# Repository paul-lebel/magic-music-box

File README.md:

# magic-music-box
A small platform for parent-configurable child entertainment and education.

## Features
1. A small box with a simple screen, UI buttons, an audio system, and a lighting system.
2. A software platform that allows parents to create custom quiz questions (eg. "What does 5+5 equal?") or games.
3. A text to speech module reads the input prompts aloud through the audio speaker for children too young to read.
4. A bluetooth module allows for music streaming to the device from a parent's cellphone.
5. Computer control of the lighting system enhances the user experience for the child.
6. Customization of the underlying PCB's silkscreen artwork is displayed through a transparent front panel.

## Requirements
RPi.GPIO, inky, gTTS, circuitpython, adafruit-circuitpython-neopixel, font_fredoka_one

## Installation
This module was developed on Raspberry Pi Zero W V1.1, but should be compatible with all newer RPi models running the latest version of Raspbian OS.
1. Ensure the OS is updated, and also ensure that Python 3 is used by default. Following the instructions here takes care of this as well as circuitpython installation: <br>
https://learn.adafruit.com/circuitpython-on-raspberrypi-linux/installing-circuitpython-on-raspberry-pi
2. Follow these instructions to install inky: <br>
https://learn.pimoroni.com/tutorial/sandyj/getting-started-with-inky-phat
3. Add the following lines to /boot/config.txt: <br>
dtoverlay=audremap, enable_jack=on <br>
dtoverlay=audremap, pins_18_19=on <br>
dtoverlay=spi1-3cs <br>
4. Download / clone this repository
5. Navigate to the base of the repository
6. Install setuptools (__pip install setuptools__)
7. Install module (__pip install .__)

## Updating Module from Repository
1. Pull changes from remote repository
2. Activate virtual environment with previous install
3. Navigate to the module directory
4. Test the module for completeness (__python setup.py test__)
5. Update module (__pip install . --upgrade__)

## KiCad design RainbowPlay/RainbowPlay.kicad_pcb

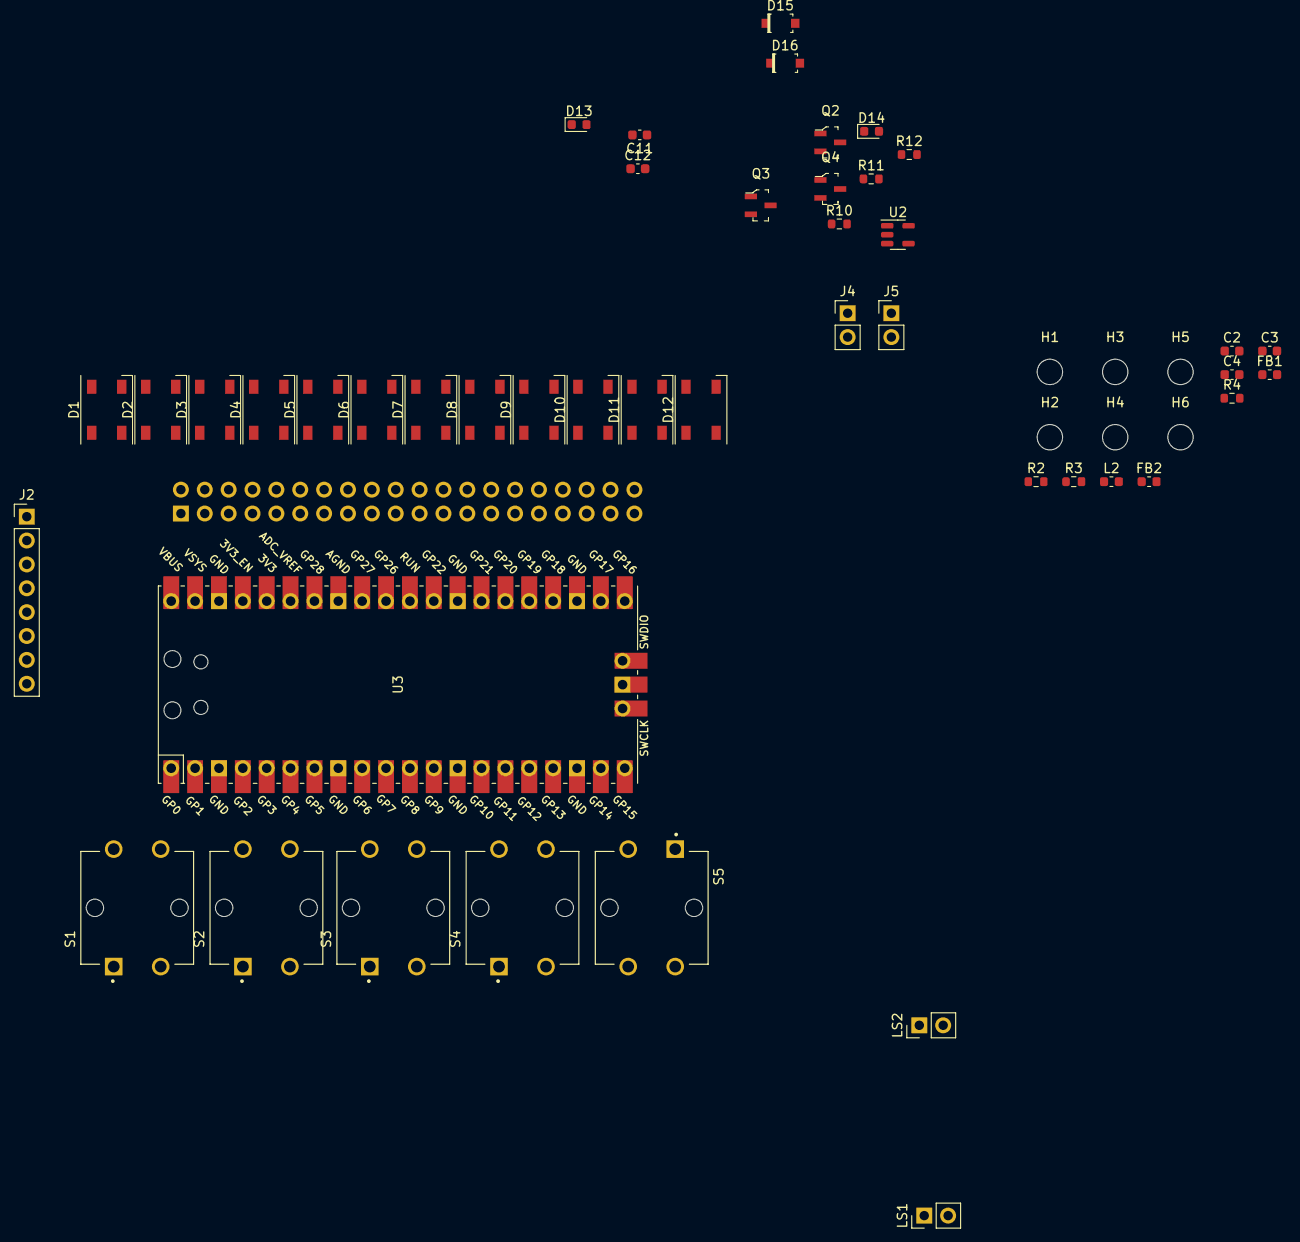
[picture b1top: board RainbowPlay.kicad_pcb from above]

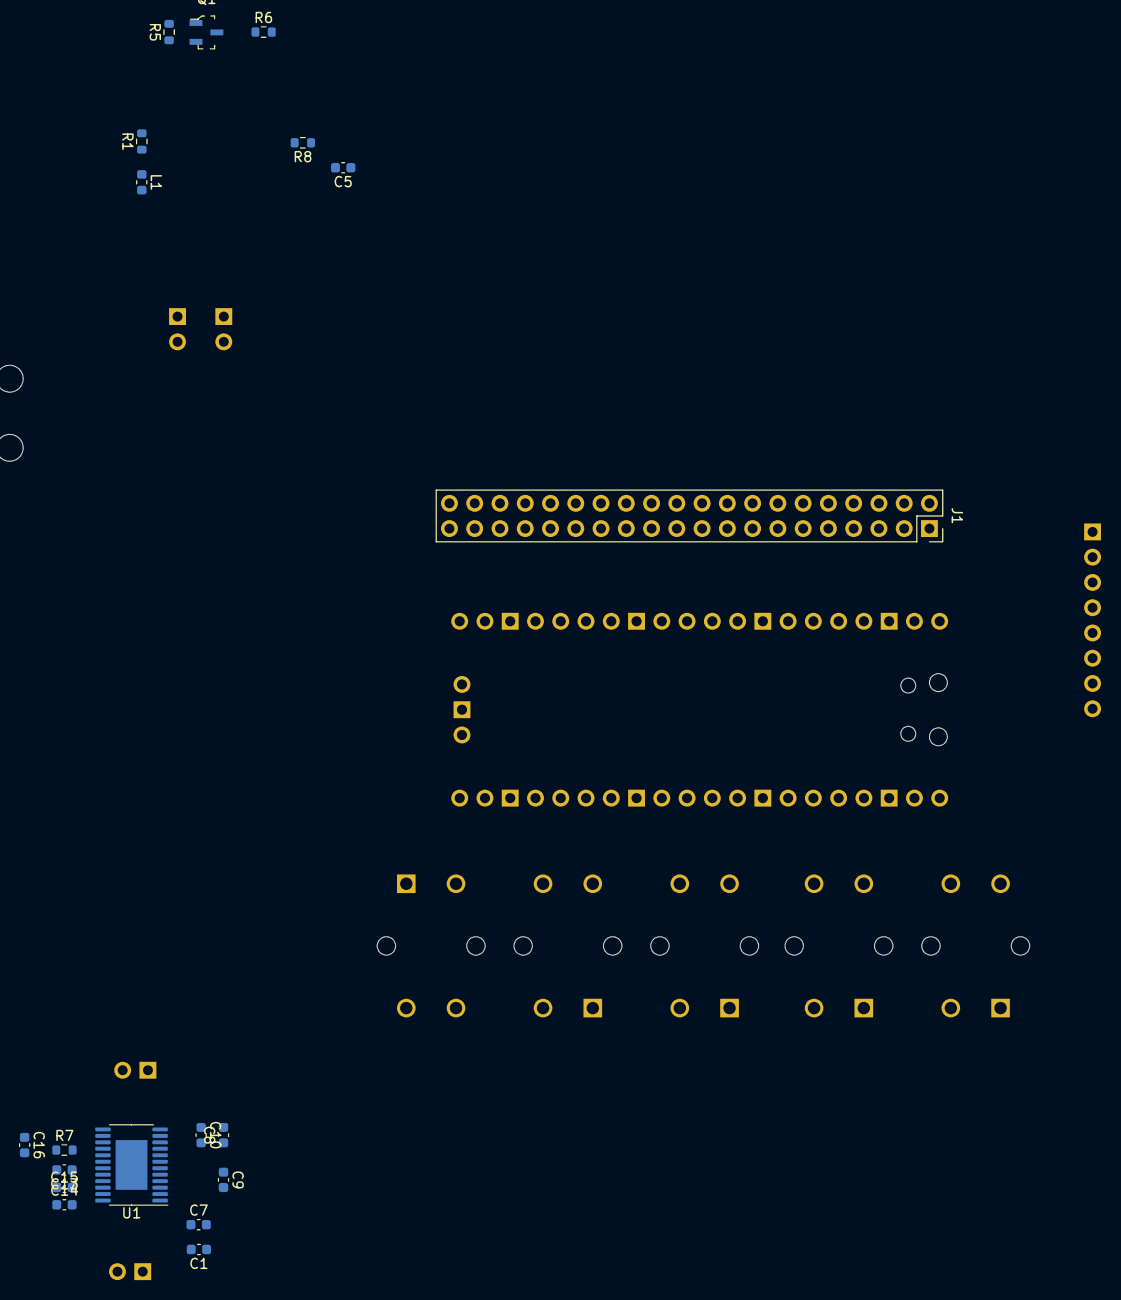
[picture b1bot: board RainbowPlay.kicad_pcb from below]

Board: 4 copper layers, 70 parts (19 on the bottom side), 52 nets, no tracks yet.

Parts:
C1, C2: 1.5uF; C_0603_1608Metric
C3, C4, C5, C7, C15, C16: 10uF; C_0603_1608Metric
C8, C9, C11, C12, C13: 0.1uF; C_0603_1608Metric
C10: 220pF; C_0603_1608Metric
C14: 1uF; C_0603_1608Metric
D1, D2, D3, D4, D5, D6, D7, D8, D9, D10, D11, D12: SK6812; LED_SK6812_PLCC4_5.0x5.0mm_P3.2mm
D13, D14: LED; LED_0603_1608Metric
D15, D16: 1N5819HW-7-F; SOD-123
FB1, FB2: FerriteBead_Small; L_0603_1608Metric
H1, H2, H3, H4, H5, H6: MountingHole; MountingHole_2.7mm
J1: GPIO_CONNECTOR; PinSocket_2x20_P2.54mm_Vertical
J2: Conn_01x08_Male; PinHeader_1x08_P2.54mm_Vertical
J4, J5: Conn_01x02_Male; PinHeader_1x02_P2.54mm_Vertical
L1, L2: 10uH; L_0603_1608Metric
LS1, LS2: Speaker; PinHeader_1x02_P2.54mm_Vertical
Q1, Q2, Q3, Q4: BSS138; SOT-23-3
R1, R3: 5R; R_0603_1608Metric
R2, R4, R5, R6, R11, R12: 10k; R_0603_1608Metric
R7: 120k; R_0603_1608Metric
R8, R10: 200R; R_0603_1608Metric
S1, S2, S3, S4, S5: B3F-4050; SW_B3F-4050
U1: TPA2001D2; HTSSOP-24-1EP_4.4x7.8mm_P0.65mm_EP3.2x5mm
U2: SN74LVC1G32DBVRG4; SOT-23-5
U3: Pico; RPi_Pico_SMD_TH

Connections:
+3V3: J1.1, Q1.1 (G), R2.2, R5.2, U2.5 (Vcc)
+5V: D1.3 (VDD), D2.3 (VDD), D3.3 (VDD), D4.3 (VDD), D5.3 (VDD), D6.3 (VDD), D7.3 (VDD), D8.3 (VDD), D9.3 (VDD), D10.3 (VDD), D11.3 (VDD), D12.3 (VDD), D13.2 (A), D15.K, D16.K, FB2.2, J1.2, J1.4, J2.1, J4.1, J5.1, R6.2, U3.39 (VSYS)
+5VA: C8.1, C9.1, C11.2, C12.1, C13.1, C15.2, C16.2, FB2.1, U1.4 (PV_DD), U1.9 (PV_DD), U1.10 (~SHUTDOWN), U1.16 (PV_DD), U1.19 (V_DD), U1.21 (PV_DD)
/AUD_L+: C3.1, U1.20 (LINP)
/AUD_L-: C4.1, U1.5 (LINN)
/AUD_R+: C5.1, U1.17 (RINP)
/AUD_R-: C7.1, U1.8 (RINN)
/AWAKE_SIG: D14.2 (A), J1.38, Q2.1 (G), R4.1, U2.1 (A)
/BTN_A: J1.11, S1.1, S1.2
/BTN_B: J1.13, S2.1, S2.2
/BTN_C: J1.27, S3.1, S3.2
/BTN_D: J1.29, S4.1, S4.2
/BTN_E: J1.31, S5.1, S5.2
/GAIN_0: J1.35, U1.3 (GAIN0)
/GAIN_1: J1.37, U1.15 (GAIN1)
/LO_BATT: J1.7, J2.8
/M1: J1.28, Q3.1 (G), R11.2
/M2: J1.36, Q4.1 (G), R12.2
/NEO: Q1.2 (S), R5.1, U3.1 (GPIO0)
/PWM_AUDIO_L: J1.32, R3.2
/PWM_AUDIO_R: J1.33, R1.2
/PWR_BTN: J1.40, R2.1, U2.2 (B)
/SPK_L+: LS1.2, U1.23 (LOUTP)
/SPK_L-: LS1.1, U1.2 (LOUTN)
/SPK_R+: LS2.2, U1.14 (ROUTP)
/SPK_R-: LS2.1, U1.11 (ROUTN)
GND: J1.20, J2.4, Q2.2 (S), R4.2, R10.1, S1.3, S1.4, S2.3, S2.4, S3.3, S3.4, S4.3, S4.4, S5.3, S5.4, U2.3 (GND), U3.28 (GND)
GND1: C8.2, C10.1, C11.1, C12.2, C13.2, C14.1, C15.1, C16.1, D1.1 (VSS), D2.1 (VSS), D3.1 (VSS), D4.1 (VSS), D5.1 (VSS), D6.1 (VSS), D7.1 (VSS), D8.1 (VSS), D9.1 (VSS), D10.1 (VSS), D11.1 (VSS), D12.1 (VSS), FB1.2, Q2.3 (D), Q3.2 (S), Q4.2 (S), R7.1, R8.1, R11.1, R12.1, U1.1 (PGND), U1.12 (PGND), U1.13 (PGND), U1.24 (PGND)
GNDA: C1.2, C2.2, C4.2, C7.2, C9.2, FB1.1, U1.6 (AGND)
unnamed: C1.1, C5.2, L1.2
unnamed: C2.1, C3.2, L2.2
unnamed: C10.2, U1.7 (COSC)
unnamed: C14.2, U1.22 (BYPASS)
unnamed: D1.2 (DIN), Q1.3 (D), R6.1
unnamed: D1.4 (DOUT), D2.2 (DIN)
unnamed: D2.4 (DOUT), D3.2 (DIN)
unnamed: D3.4 (DOUT), D4.2 (DIN)
unnamed: D4.4 (DOUT), D5.2 (DIN)
unnamed: D5.4 (DOUT), D6.2 (DIN)
unnamed: D6.4 (DOUT), D7.2 (DIN)
unnamed: D7.4 (DOUT), D8.2 (DIN)
unnamed: D8.4 (DOUT), D9.2 (DIN)
unnamed: D9.4 (DOUT), D10.2 (DIN)
unnamed: D10.4 (DOUT), D11.2 (DIN)
unnamed: D11.4 (DOUT), D12.2 (DIN)
unnamed: D13.1 (K), R8.2
unnamed: D14.1 (K), R10.2
unnamed: D15.A, J4.2, Q3.3 (D)
unnamed: D16.A, J5.2, Q4.3 (D)
unnamed: L1.1, R1.1
unnamed: L2.1, R3.1
unnamed: R7.2, U1.18 (ROSC)

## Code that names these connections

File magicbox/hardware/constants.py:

# Constants for magic_box and magic_box_screen



# Main interface buttons
BTN_A = 17
BTN_B = 27
BTN_C = 0
BTN_D = 5
BTN_E = 6

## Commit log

2021-01-02 Initial commit
    - Add initial files for RainbowPlay PCB
    - Add README.md, setup.py, __init__.py
    - Add changes.md
    - Begin work on magic_box
2021-01-03 Update README.md
    Add <br>
2021-01-03 Begin dev on MagicBox
    - Start magic_box
    - Start magic_box_screen
2021-01-03 Update magic_box.py
    Fix indentation
2021-01-03 Fix import issues. Working basic init test.
2021-10-18 Initial development in progress
2021-10-23 Development
2022-05-23 PCB dev
    - Work on power up, power down
2022-07-05 Update power/ground strategy
    - Use single power button
    - Do not disable Powerboost. Just enable/disable devices on PCB to save power when asleep
    - Add LO_BATT input
    - Clarify schematic layout of audio filtering
2022-07-30 Add pico
    - Add pico
    - Add example neopixel code
    - Test neopixel with pico (works)
2023-01-30 Another pivot
    - Change to external USB battery pack (cell phone charger w/ 8000 mA-hrs and higher I_peak). This alleviates constraints if running 2 motors at 300 mA each, with LEDs
    - Change to DRV8833 to operate motors, with pico generating PWM
    - Simplified power strategy: power down only through software. Power control using simple rocker switch and read-only SD card to protect against corruption.
2023-02-19 Remove electronics and add test scripts
2023-02-19 Remove kicad files
2023-02-19 Silly screen offset fix
2023-02-19 Add sia_clock_tft
2023-02-19 Update sia-clock-tft.py
    fix missing reference
2023-02-19 Update sia-clock-tft.py
    silly bug
2023-02-19 Update sia-clock-tft.py
    another silly bug
2023-02-19 Update sia-clock-tft.py
    missing font definition
2023-02-19 Update sia-clock-tft.py
    Update layout for clock display
2023-02-19 Update sia-clock-tft.py
    adjust spacings and font size
2023-02-19 Update sia-clock-tft.py
    adjust font size and layout
2023-02-19 Update sia-clock-tft.py
    add loop
2023-02-19 Update sia-clock-tft.py
    - Remove black rectangle display to avoid flashing
    - Test red clock (temp)
2023-02-19 Update sia-clock-tft.py
    Revert to 7:30pm bedtime
2023-02-19 Update sia-clock-tft.py
    add rotation
2023-02-19 Add backlight button and weather update interval
2023-02-19 Update sia-clock-tft.py
    More silly fixes
2023-02-19 Update sia-clock-tft.py
    More fixes
2023-02-19 Update sia-clock-tft.py
    Add falling edge logic so screen doesn't always turn off
2023-02-20 Added funny weather images
2023-02-20 Update sia-clock-tft.py
    Silly bug fix
2023-02-20 Add pufferfish cloud
2023-02-20 Add wind
2023-02-20 Update sia-clock-tft.py
    adjust location of weather image
2023-02-20 Update sia-clock-tft.py
    Restore actual weather indication
2023-02-20 Make it storm
2023-02-20 Update sia-clock-tft.py
    - Revert to actual weather indication
    - add temperature color
2023-02-20 Update sia-clock-tft.py
    Fix silly bug
2023-02-21 Update sia-clock-tft.py
    Fix weekday time comparison
2023-03-09 Update sia-clock-tft.py
    Making time color more granular
2023-03-09 Update sia-clock-tft.py
    add print statement for loop time
2023-03-09 Update sia-clock-tft.py
    add other print statements
2023-03-09 Update sia-clock-tft.py
    weather check
2023-06-18 Remove phat stuff
2023-06-18 Refactor
2023-06-18 Continue refactoring
2023-07-16 Dev
    - Add TSOP38238
    - Start adding GPIO breakout expansion
    - Rename sender.py
    - Start pico.py
    - Begin making sm

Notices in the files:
RainbowPlay/RainbowPlay.kicad_pcb:
This PCB design is licensed under MIT Open Source License.
